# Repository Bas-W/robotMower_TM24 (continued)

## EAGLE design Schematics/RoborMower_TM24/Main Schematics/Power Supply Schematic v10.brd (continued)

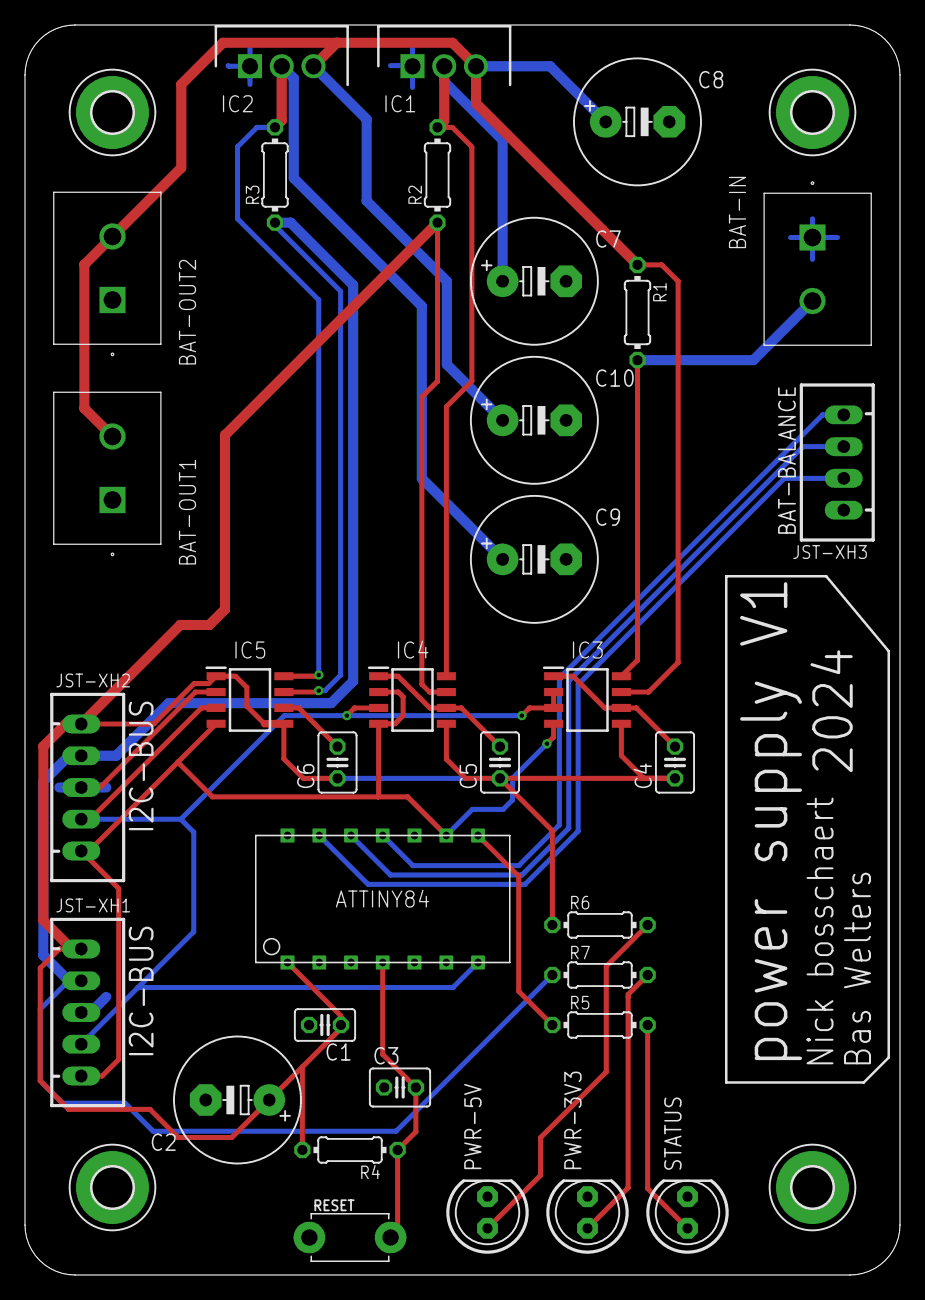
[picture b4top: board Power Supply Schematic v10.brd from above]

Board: 2 copper layers, 70.0 x 100.0 mm, 37 parts (0 on the bottom side), 17 nets.

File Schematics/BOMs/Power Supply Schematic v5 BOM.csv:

Part;Value;Device;Package;Description;ARROW_PART_NUMBER;ARROW_PRICE-STOCK;DESCRIPTION;HEIGHT;MANUFACTURER_NAME;MANUFACTURER_PART_NUMBER;MOUSER2_PART_NUMBER;MOUSER2_PRICE-STOCK;MOUSER_PART_NUMBER;MOUSER_PRICE-STOCK;POPULARITY;SPICEPREFIX
BAT-IN;1747993;1747993;1747993;PCB header, nominal cross section: 2.5 mm?, color: green, nominal current: 12 A, rated voltage (III/2): 320 V, contact surface: Gold, type of contact: Male connector, Number of potentials: 2, Number of rows: 1, Number of positions per row: 2, number of connections: 2, product range: MSTBVA 2,5/..-G, pitch: 5.08 mm, mounting: Wave soldering, pin layout: Linear pinning, solder pin [P]: 3.9 mm, Stecksystem: CLASSIC COMBICON, Locking: without, type of packaging: packed in cardboard;;;PCB header, nominal cross section: 2.5 mm?, color: green, nominal current: 12 A, rated voltage (III/2): 320 V, contact surface: Gold, type of contact: Male connector, Number of potentials: 2, Number of rows: 1, Number of positions per row: 2, number of connections: 2, product range: MSTBVA 2,5/..-G, pitch: 5.08 mm, mounting: Wave soldering, pin layout: Linear pinning, solder pin [P]: 3.9 mm, Stecksystem: CLASSIC COMBICON, Locking: without, type of packaging: packed in cardboard;12.15mm;Phoenix Contact;1747993;;;651-1747993;https://www.mouser.co.uk/ProductDetail/Phoenix-Contact/17479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;;
BAT-OUT1;1747993;1747993;1747993;PCB header, nominal cross section: 2.5 mm?, color: green, nominal current: 12 A, rated voltage (III/2): 320 V, contact surface: Gold, type of contact: Male connector, Number of potentials: 2, Number of rows: 1, Number of positions per row: 2, number of connections: 2, product range: MSTBVA 2,5/..-G, pitch: 5.08 mm, mounting: Wave soldering, pin layout: Linear pinning, solder pin [P]: 3.9 mm, Stecksystem: CLASSIC COMBICON, Locking: without, type of packaging: packed in cardboard;;;PCB header, nominal cross section: 2.5 mm?, color: green, nominal current: 12 A, rated voltage (III/2): 320 V, contact surface: Gold, type of contact: Male connector, Number of potentials: 2, Number of rows: 1, Number of positions per row: 2, number of connections: 2, product range: MSTBVA 2,5/..-G, pitch: 5.08 mm, mounting: Wave soldering, pin layout: Linear pinning, solder pin [P]: 3.9 mm, Stecksystem: CLASSIC COMBICON, Locking: without, type of packaging: packed in cardboard;12.15mm;Phoenix Contact;1747993;;;651-1747993;https://www.mouser.co.uk/ProductDetail/Phoenix-Contact/17479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;;
BAT-OUT2;1747993;1747993;1747993;PCB header, nominal cross section: 2.5 mm?, color: green, nominal current: 12 A, rated voltage (III/2): 320 V, contact surface: Gold, type of contact: Male connector, Number of potentials: 2, Number of rows: 1, Number of positions per row: 2, number of connections: 2, product range: MSTBVA 2,5/..-G, pitch: 5.08 mm, mounting: Wave soldering, pin layout: Linear pinning, solder pin [P]: 3.9 mm, Stecksystem: CLASSIC COMBICON, Locking: without, type of packaging: packed in cardboard;;;PCB header, nominal cross section: 2.5 mm?, color: green, nominal current: 12 A, rated voltage (III/2): 320 V, contact surface: Gold, type of contact: Male connector, Number of potentials: 2, Number of rows: 1, Number of positions per row: 2, number of connections: 2, product range: MSTBVA 2,5/..-G, pitch: 5.08 mm, mounting: Wave soldering, pin layout: Linear pinning, solder pin [P]: 3.9 mm, Stecksystem: CLASSIC COMBICON, Locking: without, type of packaging: packed in cardboard;12.15mm;Phoenix Contact;1747993;;;651-1747993;https://www.mouser.co.uk/ProductDetail/Phoenix-Contact/17479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;;
C1;0.1uF;C-EU025-025X050;C025-025X050;CAPACITOR, European symbol;;;;;;;;;;;65;C
C2;10uF;CPOL-EUE5-10.5;E5-10,5;POLARIZED CAPACITOR, European symbol;;;;;;;;;;;23;C
C3;0.1uF;C-EU025-030X050;C025-030X050;CAPACITOR, European symbol;;;;;;;;;;;14;C
C4;0.1uF;C-EU025-030X050;C025-030X050;CAPACITOR, European symbol;;;;;;;;;;;14;C
C5;0.1uF;C-EU025-030X050;C025-030X050;CAPACITOR, European symbol;;;;;;;;;;;14;C
C6;0.1uF;C-EU025-030X050;C025-030X050;CAPACITOR, European symbol;;;;;;;;;;;14;C
C7;10uF;CPOL-EUE5-10.5;E5-10,5;POLARIZED CAPACITOR, European symbol;;;;;;;;;;;23;C
C8;10uF;CPOL-EUE5-10.5;E5-10,5;POLARIZED CAPACITOR, European symbol;;;;;;;;;;;23;C
C9;10uF;CPOL-EUE5-10.5;E5-10,5;POLARIZED CAPACITOR, European symbol;;;;;;;;;;;23;C
C10;10uF;CPOL-EUE5-10.5;E5-10,5;POLARIZED CAPACITOR, European symbol;;;;;;;;;;;23;C
H1;MOUNT-PAD-ROUND3.3;MOUNT-PAD-ROUND3.3;3,3-PAD;MOUNTING PAD, round;;;;;;;;;;;1;
H2;MOUNT-PAD-ROUND3.3;MOUNT-PAD-ROUND3.3;3,3-PAD;MOUNTING PAD, round;;;;;;;;;;;1;
H3;MOUNT-PAD-ROUND3.3;MOUNT-PAD-ROUND3.3;3,3-PAD;MOUNTING PAD, round;;;;;;;;;;;1;
H4;MOUNT-PAD-ROUND3.3;MOUNT-PAD-ROUND3.3;3,3-PAD;MOUNTING PAD, round;;;;;;;;;;;1;
IC1;LM1117T-5.0_NOPB;LM1117T-5.0_NOPB;TO254P470X1028X1955-3P;Space saving 800-mA low-dropout linear regulator with internal current limit;;;Space saving 800-mA low-dropout linear regulator with internal current limit;4.7mm;Texas Instruments;LM1117T-5.0/NOPB;926-LM1117T-50/NOPB;https://www.mouser.com/Search/Refine.aspx?Keyword=926-LM1117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;;;;
IC2;LM1117T-3.3_NOPB;LM1117T-3.3_NOPB;TO254P470X1028X1955-3P;800mA,3.3V,LDO Voltage Reg.,LM1117T-3.3 Texas Instruments LM1117T-3.3/NOPB, LDO Voltage Regulator, 800mA, 3.3 V;;;800mA,3.3V,LDO Voltage Reg.,LM1117T-3.3 Texas Instruments LM1117T-3.3/NOPB, LDO Voltage Regulator, 800mA, 3.3 V;4.7mm;Texas Instruments;LM1117T-3.3/NOPB;;;;;;
IC3;INA219BIDR;INA219BIDR;SOIC127P600X175-8N;26-V, Bidirectional, Zero-Drift, High-Side, I2C Out Current/Power Monitor;;;26-V, Bidirectional, Zero-Drift, High-Side, I2C Out Current/Power Monitor;1.75mm;Texas Instruments;INA219BIDR;;;595-INA219BIDR;https://www.mouser.co.uk/ProductDetail/Texas-Instruments/INA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;;
IC4;INA219BIDR;INA219BIDR;SOIC127P600X175-8N;26-V, Bidirectional, Zero-Drift, High-Side, I2C Out Current/Power Monitor;;;26-V, Bidirectional, Zero-Drift, High-Side, I2C Out Current/Power Monitor;1.75mm;Texas Instruments;INA219BIDR;;;595-INA219BIDR;https://www.mouser.co.uk/ProductDetail/Texas-Instruments/INA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;;
IC5;INA219BIDR;INA219BIDR;SOIC127P600X175-8N;26-V, Bidirectional, Zero-Drift, High-Side, I2C Out Current/Power Monitor;;;26-V, Bidirectional, Zero-Drift, High-Side, I2C Out Current/Power Monitor;1.75mm;Texas Instruments;INA219BIDR;;;595-INA219BIDR;https://www.mouser.co.uk/ProductDetail/Texas-Instruments/INA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;;
JST-XH1;I2C-BUS;JST-XH-05-PIN-LONG-PAD;JST-XH-05-PACKAGE-LONG-PAD;JST XH Connector 2 Pin;;;;;;;;;;;;
JST-XH2;I2C-BUS;JST-XH-05-PIN-LONG-PAD;JST-XH-05-PACKAGE-LONG-PAD;JST XH Connector 2 Pin;;;;;;;;;;;;
JST-XH3;BAT-BALANCE;JST-XH-04-PIN-LONG-PAD;JST-XH-04-PACKAGE-LONG-PAD;JST XH Connector 2 Pin;;;;;;;;;;;;
PWR-3V3;GN;LED5MM;LED5MM;LED;;;;;;;;;;;;
PWR-5V;GN;LED5MM;LED5MM;LED;;;;;;;;;;;;
R1;12m;R-EU_0204/7;0204/7;RESISTOR, European symbol;;;;;;;;;;;79;R
R2;tbd;R-EU_0204/7;0204/7;RESISTOR, European symbol;;;;;;;;;;;79;R
R3;tbd;R-EU_0204/7;0204/7;RESISTOR, European symbol;;;;;;;;;;;79;R
R4;10k;R-EU_0204/7;0204/7;RESISTOR, European symbol;;;;;;;;;;;79;R
R5;220;R-EU_0204/7;0204/7;RESISTOR, European symbol;;;;;;;;;;;79;R
R6;220;R-EU_0204/7;0204/7;RESISTOR, European symbol;;;;;;;;;;;79;R
R7;220;R-EU_0204/7;0204/7;RESISTOR, European symbol;;;;;;;;;;;79;R
RESET;;SWITCH_PUSHBUTTONEVQ-PE;TACT_PANA-EVQ;Buttons;;;;;;;;;;;;
STATUS;RD;LED5MM;LED5MM;LED;;;;;;;;;;;;
U$1;ATTINY84DIP;ATTINY84DIP;ATTINY84(DIP);;;;;;;;;;;;;

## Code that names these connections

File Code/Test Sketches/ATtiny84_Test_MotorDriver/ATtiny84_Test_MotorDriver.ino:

#define Q1M1 A0
#define Q2M1 A1
#define Q3M1 A2
#define Q4M1 A3

#define Q1M2 B0
#define Q2M2 B1
#define Q3M2 PB2
#define Q4M2 A7

#define statusLED A5

void setup() {
  // put your setup code here, to run once:
pinMode(Q1M1, OUTPUT);
pinMode(Q2M1, OUTPUT);
pinMode(Q3M1, OUTPUT);
pinMode(Q4M1, OUTPUT);

pinMode(Q1M2, OUTPUT);
pinMode(Q2M2, OUTPUT);
pinMode(Q3M2, OUTPUT);
pinMode(Q4M2, OUTPUT);

pinMode(statusLED, OUTPUT);

digitalWrite(statusLED, HIGH);
}

void Forward(int speed){
  digitalWrite(Q1M1, LOW);
  digitalWrite(Q2M1, LOW);
  digitalWrite(Q3M1, LOW);
  digitalWrite(Q4M1, LOW);

  digitalWrite(Q1M2, LOW);
  digitalWrite(Q2M2, LOW);
  digitalWrite(Q3M2, LOW);
  digitalWrite(Q4M2, LOW);

  digitalWrite(Q1M1, HIGH);
  digitalWrite(Q2M1, LOW);
  digitalWrite(Q3M1, LOW);
  digitalWrite(Q4M1, HIGH);

  digitalWrite(Q1M2, HIGH);
  digitalWrite(Q2M2, LOW);
  digitalWrite(Q3M2, LOW);
  digitalWrite(Q4M2, HIGH);
}

void Backward(int speed){
  digitalWrite(Q1M1, LOW);
  digitalWrite(Q2M1, LOW);
  digitalWrite(Q3M1, LOW);
  digitalWrite(Q4M1, LOW);

  digitalWrite(Q1M2, LOW);
  digitalWrite(Q2M2, LOW);
  digitalWrite(Q3M2, LOW);
  digitalWrite(Q4M2, LOW);

  digitalWrite(Q1M1, LOW);
  digitalWrite(Q2M1, HIGH);
  digitalWrite(Q3M1, HIGH);
  digitalWrite(Q4M1, LOW);

  digitalWrite(Q1M2, LOW);
  digitalWrite(Q2M2, HIGH);
  digitalWrite(Q3M2, HIGH);
  digitalWrite(Q4M2, LOW);
}

void loop() {
  // put your main code here, to run repeatedly:
Forward(255);
delay(1000);
Backward(255);
delay(1000);
}

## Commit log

2024-02-24 Adding Features List
    Added the Features list
2024-02-24 Adding to features
2024-02-27 Updated to preferences Stefan
2024-02-28 Adding the different modules
2024-02-28 Adding the breakout controller
2024-02-28 Eagle library
    Added the Eagle Library with currently only the ATtiny84 in SOIC and DIP format
2024-02-28 Create bla
2024-02-28 Rename README.md to Features.md
2024-02-28 Added the base Schematics
2024-02-29 Adding current Schematics
2024-02-29 Changed names
2024-02-29 adding the individual schematics and the main library for eagle
2024-02-29 added adafruit library
2024-03-07 Adding Schematics
2024-03-07 Programming
    Added the explanations for programming the ATtiny84 and for programming the ESP32S3
2024-03-07 Basic code
    Adding the basic test programs
2024-03-07 Create Gerbers
2024-03-07 Create test
2024-03-07 Gerbers
    Adding the gerbers of the ultrasonic pcb and the MCU pcb
2024-03-08 Adding the BOMs
2024-03-08 BOMS
2024-03-10 Update README.md to include features
2024-03-10 italic features
2024-03-10 changed 12mOhm and 39mOhm resistors
2024-03-19 reichelt bpom
2024-03-19 Changing the programming methods
2024-03-21 Update I2C_Scanning file
2024-03-27 added the basic sketches for reading the ultrasonic sensor and for the basic I2C communication
2024-04-16 etdstgds
2024-04-17 added INA219 functionality to motor test program
2024-04-17 mainly lcd screens
2024-04-18 sketches
2024-04-18 Huppakey
2024-04-18 libraries
2024-04-18 updated features
2024-04-18 Changing features
2024-04-18 adding libraries
2024-04-18 update of the schematic
2024-04-18 Create Notes
2024-04-18 Rename Notes to Notes.md
2024-04-18 Adding my notes
2024-04-18 Als/Dan-fout verbeterd
2024-04-18 adding the schematic and board files from fusion and the libraries
2024-04-18 Adding the reference to the original fusion files
2024-04-18 updates to ESP32s3.md
2024-04-18 update to notes
